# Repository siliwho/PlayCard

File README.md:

# PlayCard

### **Real-time Embedded UI with Cloud Connectivity and Offline Caching**

This project implements a compact handheld device with a modular application framework, capable of rendering a real-time user interface, running simple games, displaying images, and managing a TODO list. The system integrates a dual-microcontroller architecture combining deterministic UI performance with modern IoT connectivity.

ok

---

## **1. Overview**

The device uses:

- **STM32F411CEU6** as the real-time computation and display controller
- **ESP32-WROOM-32** as the networking, HTTP backend, and persistent storage module
- **SSD1306 OLED display** for user interface
- **Custom UART protocol** for inter-MCU communication

The architecture separates time-critical operations from network-related tasks, ensuring stable frame rendering and predictable behavior irrespective of WiFi conditions.

---

## **2. Key Features**

### STM32 Firmware

- Real-time display rendering using SSD1306
- FreeRTOS-based task scheduling
- Pong, Snake, and menu-driven application system
- GPIO interrupt-driven input handling
- PWM-based buzzer feedback
- Efficient frame buffering and UI drawing
- Deterministic performance independent of WiFi latency

### ESP32 Firmware

- Non-blocking WiFi connectivity
- HTTP GET/POST communication with backend server
- SPIFFS filesystem for persistent offline caching
- JSON parsing for TODO list management
- Binary transfer of image data to STM32
- Automatic fallback to cached data when WiFi is unavailable
- Custom message-framed UART protocol with checksum validation

---

## **3. System Architecture**

### STM32 Responsibilities

- Main application logic
- User interface and display updates
- Input processing
- Execution of games and utilities
- Rendering image and TODO data received from ESP32

### ESP32 Responsibilities

- WiFi connection management
- Backend synchronization (images, TODO list, toggle states)
- File-based offline storage (SPIFFS)
- Data serialization/deserialization
- Responding to STM32 data requests

This separation reflects industry standards for embedded IoT devices where networking and control loops are isolated to ensure stability.

---

## **4. Offline Operation and Memory Handling**

The ESP32 maintains cached copies of backend data in its SPIFFS partition:

- `image.bin` — raw binary image buffer
- `todos.json` — serialized list of tasks

At boot:

1. ESP32 loads both files into RAM if they exist.
2. STM32 requests data as needed.
3. If WiFi is available, ESP32 attempts to fetch updated data from the backend.
4. If WiFi is unavailable, ESP32 immediately returns cached data.

This ensures:

- Instant boot and UI responsiveness
- No dependency on WiFi availability
- Consistent data availability for the STM32
- Reduced backend load due to on-demand fetching

---

## **5. Communication Protocol**

A reliable framed UART protocol is used:

- Sync byte: `0xAA`
- Message type
- Payload length (little endian)
- Payload
- XOR checksum

Supported message types include:

- `MSG_REQ_IMAGE`
- `MSG_REQ_TODOS`
- `MSG_IMAGE_FULL`
- `MSG_TODO_FULL`
- `MSG_TODO_TOGGLE`

Checksum validation ensures corruption detection on noisy UART lines. Failed checksums are discarded and the parser resets to sync state, preventing protocol desynchronization.

---

## **6. Error Handling and Fault Tolerance**

### Networking Errors

- Non-blocking WiFi initiation prevents system stalling.
- HTTP failures fall back to cached SPIFFS data.
- ESP32 logs status codes for debugging (200, 404, 500, timeouts).

### UART Errors

- Checksum mismatches are detected and ignored.
- Invalid or unknown message types do not affect system state.
- Fixed-sized reception buffers prevent overflows.

### Storage Errors

- Missing SPIFFS files trigger safe defaults.
- Corrupted JSON files are detected using `deserializeJson` return codes.
- Partial or invalid binary file reads mark image as invalid.

### STM32 RTOS Stability

- Tasks are designed to avoid long blocking operations.
- Menu loop enforces periodic yielding (`osDelay`) to maintain UI responsiveness.

---

## **7. Hardware Summary**

- STM32F411CEU6 microcontroller
- ESP32-WROOM-32 WiFi module
- SSD1306 128×64 OLED display (I2C)
- Momentary push buttons for UI control
- PWM-driven buzzer
- UART, I2C, GPIO and timer peripherals utilized
- Perfboard-based hardware assembly and soldering

---

## **8. Engineering Skills Demonstrated**

- Real-time embedded development (C, FreeRTOS)
- Low-level driver integration (GPIO, I2C, PWM, UART)
- Reliable inter-MCU communication protocol design
- IoT backend integration using HTTP and JSON
- Efficient use of SPI Flash filesystems (SPIFFS)
- Fault-tolerant system design
- Memory-constrained data handling
- Architecture aligned with industrial IoT practices

---

## **9. Repository Structure**

```
/stm32/
    Core/Src/
    Core/Inc/
    SSD1306/
    Apps/
        menu/
        pong/
        todo/
        image_viewer/
    comm.c

/esp32/
    main.cpp
    storage/
    http_client/
    uart_protocol/
```

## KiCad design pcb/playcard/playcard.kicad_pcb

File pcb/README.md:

### 1. The ILI9341 TFT Display (Hardware SPI)

To get the highest frame rate possible for games, you should connect the display to **SPI1**. On the STM32F411, SPI1 is on the APB2 bus, which can run at up to 50MHz, making it the fastest SPI peripheral on the board.

- **SCK** ➔ **PA5** (SPI1_SCK)
- **SDI\_(MOSI)** ➔ **PA7** (SPI1_MOSI)
- **SDO\_(MISO)** ➔ **PA6** (SPI1*MISO - \_Note: You only need this if you plan to read pixel data back from the screen. If you are only drawing to it, you can leave this unconnected.*)
- **CS** ➔ **PB0** (Standard GPIO Output - manual chip select)
- **D/C** ➔ **PB1** (Standard GPIO Output - Data/Command toggle)
- **RESET** ➔ **PB2** (Standard GPIO Output)
- **LED** ➔ **3V3** (This turns the backlight on full blast. Alternatively, wire it to **PA8** later if you want to write a hardware PWM driver for brightness control).

### 2. The Buttons (SW1 - SW6)

Since the switches are tied to `GND` on one side, you need to connect the other side to standard GPIO pins and configure them as **Inputs with Internal Pull-Up Resistors** in the bare-metal code. When a button is pressed, the pin will read `0` (LOW).

I recommend using a contiguous block of pins on the same port so reading the buttons is a single, fast register read (e.g., reading the `GPIOB->IDR` register).

- **SW1** ➔ **PB12**
- **SW2** ➔ **PB13**
- **SW3** ➔ **PB14**
- **SW4** ➔ **PB15**
- **SW5** ➔ **PA0**
- **SW6** ➔ **PA1**

### 3. The ESP32-S3-ZERO (UART Bluetooth Bridge)

the schematic already has this handled perfectly with the net labels! Just to confirm the logic:

- **BlackPill PA9 (TX1)** is correctly routed to **ESP32 RX**.
- **BlackPill PA10 (RX1)** is correctly routed to **ESP32 TX**.
- **Crucial step:** Ensure the `GND` net for the BlackPill, the Display, and the ESP32 are all tied together so the UART and SPI signals share the same reference voltage.

### 4. Ignored Pins (For Now)

- **Touch Pins (T_CLK, T_CS, etc.):** Unless the games require a touchscreen, leave these disconnected to save GPIO and complexity.
- **SD Card Pins:** Leave these unconnected for now. You can always wire them to SPI2 later if you decide to load game assets from an SD card.

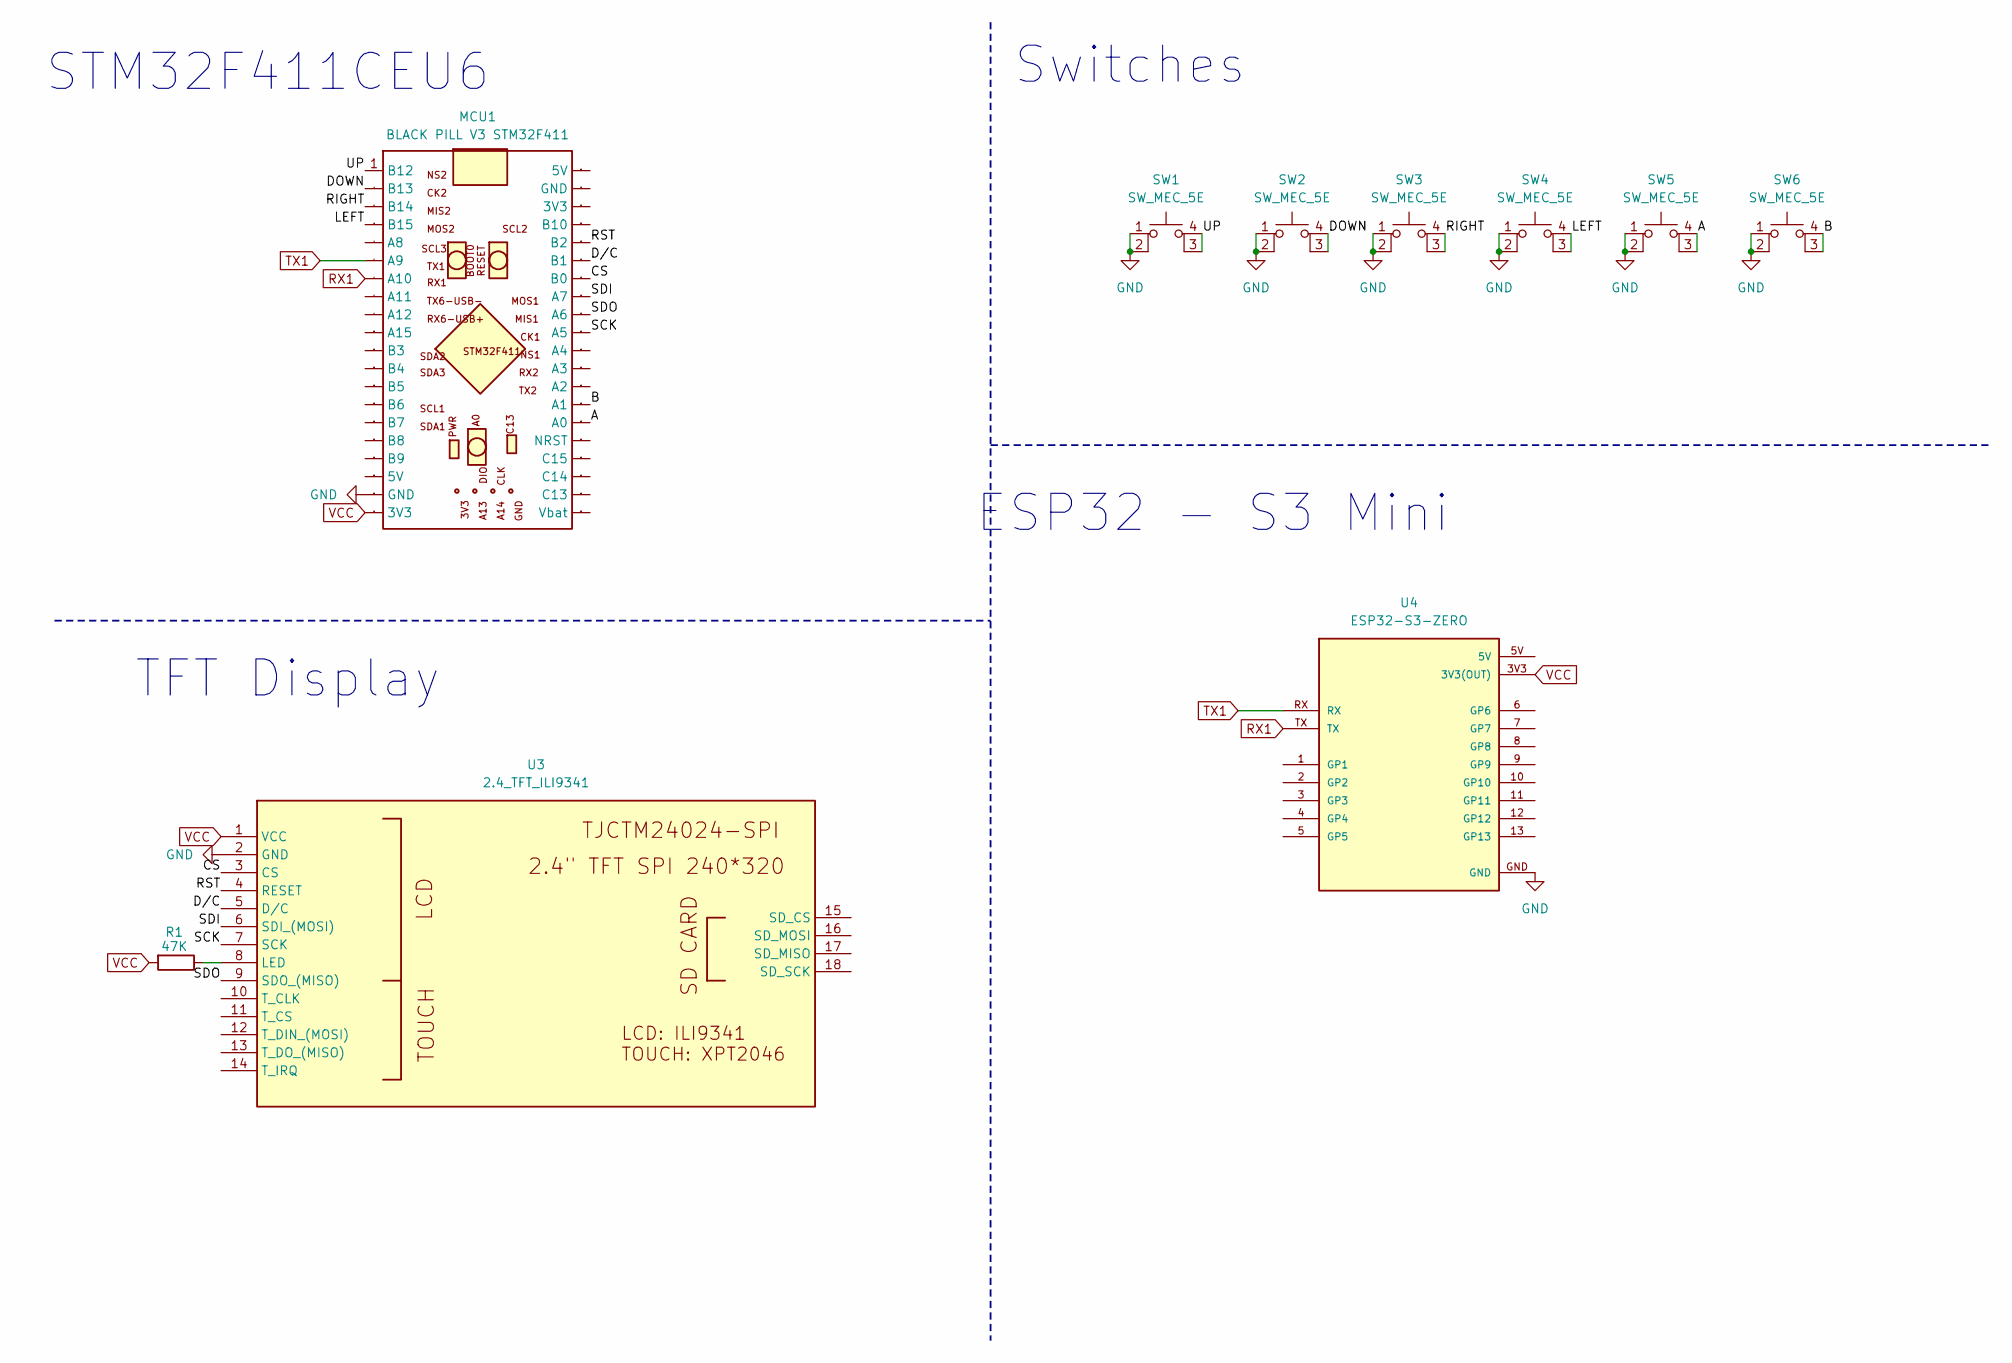
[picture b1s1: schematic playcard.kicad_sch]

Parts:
MCU1: BLACK PILL V3 STM32F411; BLACK PILL V3; Manufacturer Part Black Pill V3
R1: 47K; R_0612_1632Metric
SW1, SW2, SW3, SW4, SW5, SW6: SW_MEC_5E; 6x6mm_tactile_sw_tht
U3: 2.4_TFT_ILI9341; Manufacturer Part siliwho
U4: ESP32-S3-ZERO; MODULE_ESP32-S3-ZERO

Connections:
/A: MCU1.35 (A0), SW5.3 (K), SW5.4 (A)
/B: MCU1.34 (A1), SW6.3 (K), SW6.4 (A)
/CS: MCU1.27 (B0), U3.3 (CS)
/DOWN: MCU1.2 (B13), SW2.3 (K), SW2.4 (A)
/D/C: MCU1.26 (B1), U3.5 (D/C)
/LEFT: MCU1.4 (B15), SW4.3 (K), SW4.4 (A)
/RIGHT: MCU1.3 (B14), SW3.3 (K), SW3.4 (A)
/RST: MCU1.25 (B2), U3.4 (RESET)
/SCK: MCU1.30 (A5), U3.7 (SCK)
/SDI: MCU1.28 (A7), U3.6 (SDI_(MOSI))
/SDO: MCU1.29 (A6), U3.9 (SDO_(MISO))
/UP: MCU1.1 (B12), SW1.3 (K), SW1.4 (A)
GND: MCU1.19 (GND), SW1.1, SW1.2, SW2.1, SW2.2, SW3.1, SW3.2, SW4.1, SW4.2, SW5.1, SW5.2, SW6.1, SW6.2, U3.2 (GND), U4.GND
unnamed: R1.1, U3.8 (LED)
RX1: MCU1.7 (A10), U4.TX
TX1: MCU1.6 (A9), U4.RX
VCC: MCU1.20 (3V3), R1.2, U3.1 (VCC), U4.3V3 (3V3(OUT))

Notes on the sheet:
Switches
ESP32 - S3 Mini
TFT Display
STM32F411CEU6

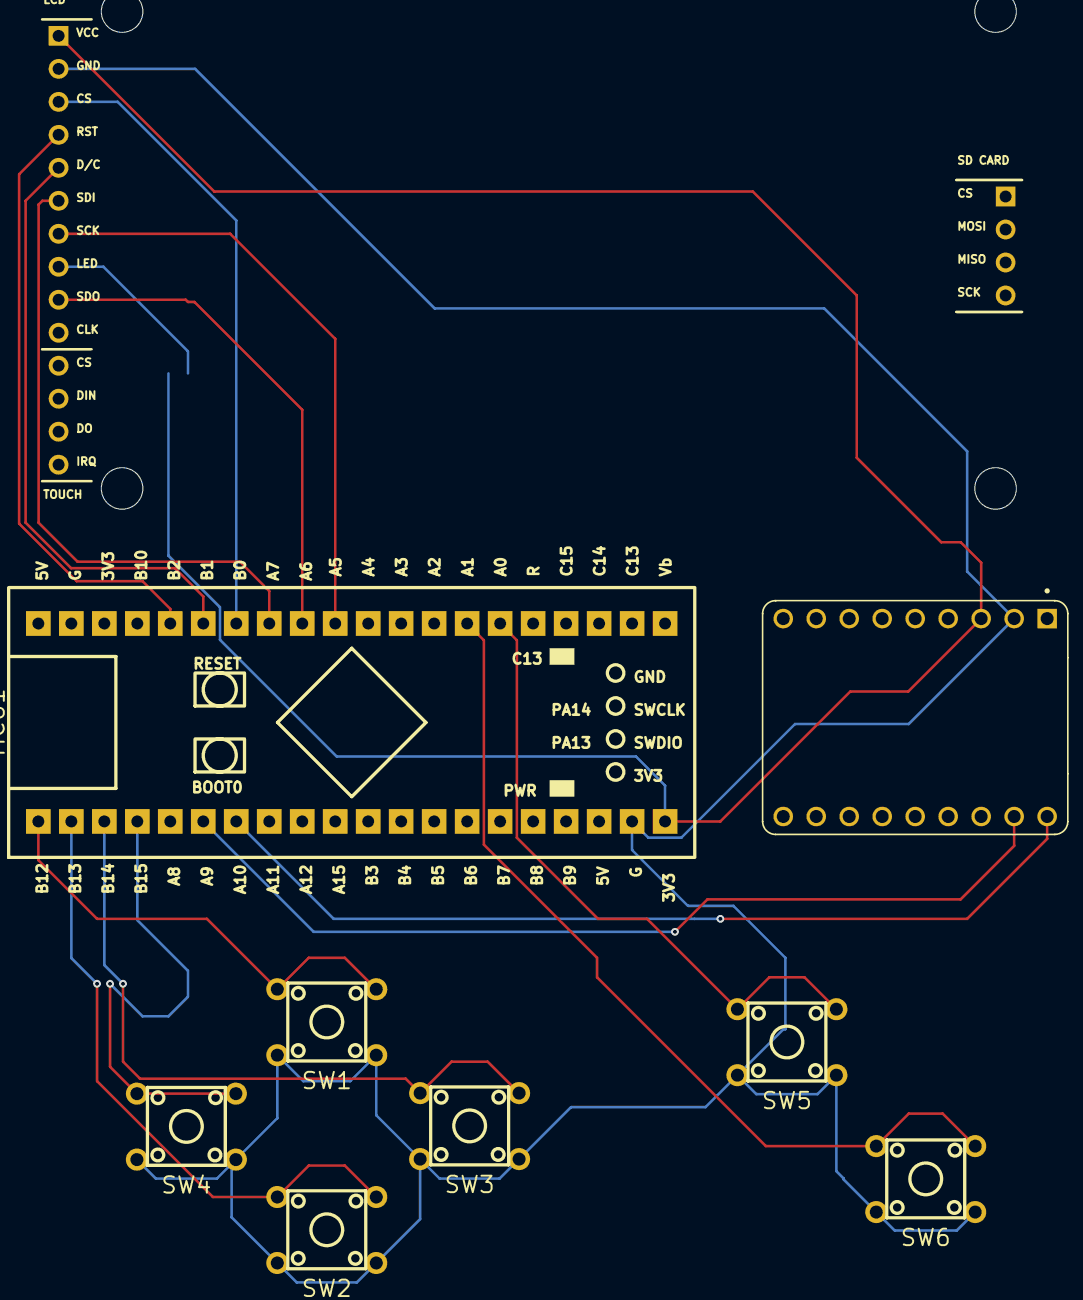
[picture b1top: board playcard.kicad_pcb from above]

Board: 2 copper layers, 10 parts (1 on the bottom side), 17 nets.

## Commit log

2025-12-05 moved project from stm32cudeide default directory
2026-03-04 started playcard pcb
2026-03-05 updated pcb and readme
